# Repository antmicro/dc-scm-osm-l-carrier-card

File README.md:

# DC-SCM Carrier Card for OSM-L SoMs

Copyright (c) 2025 [Antmicro](https://www.antmicro.com)

## Overview

This project includes open hardware design files for a DC-SCM compliant PCB that supports System on Modules following the [OSM-L](https://sget.org/standards/osm/) standard specified by the SGet group.
The DC-SCM follows the interface and mechanical outline described in the 2.1 revision of the [DC-SCM standard](https://drive.google.com/file/d/1-SdSQvSWy5pNN_kBiyztblxE4jdyUe9W/view?usp=sharing) specified by the Open Compute Project community.
Apart from establishing a base DC-SCM compliant platform, the design includes a series of breakout connectors, jumpers and other supplementary circuitry for developing BMC software features for security, reliability, commissioning and benchmarking.

This DC-SCM card has been designed as a carrier board to an L-sized [OSM design](https://github.com/antmicro/osm-l-bmc-som) that combines a Lattice FPGA and an NXP i.MX943 series Application Processor (AP).

The PCB design files were prepared in [KiCad](kicad.org/download) 9.x

## Key features

* Landing pad for OSM-L type of SoM
* Realtek 1Gb Ethernet PHY (Realtek [RTL8211FDI-CG](https://openhardware.antmicro.com/components/realtek-rtl8211fdi-cg))
* ITE [IT6251](https://openhardware.antmicro.com/components/ite-tech-it6251) LVDS-DisplayPort bridge
* USB-C port with FTDI [FT4232H](https://openhardware.antmicro.com/components/ftdi-chip-ft4232h-56q-reel/) for SoM debug and software integration
* USB-C port connected to the OSM-L SoM pads
* USB-C port connected to the HPM
* M.2 (key-M) expansion slot connected to the HPM
* Slot for removable BIOS memories connected directly to the HPM
* Optional on-board TPM connector

## Project structure

The main directory contains KiCad PCB project files, a LICENSE and a README.
The remaining files are stored in the following directories:

* `doc` - contains board schematic
* `img` contains graphics for this README

## Licensing

This project is published under the [Apache-2.0](LICENSE) license.

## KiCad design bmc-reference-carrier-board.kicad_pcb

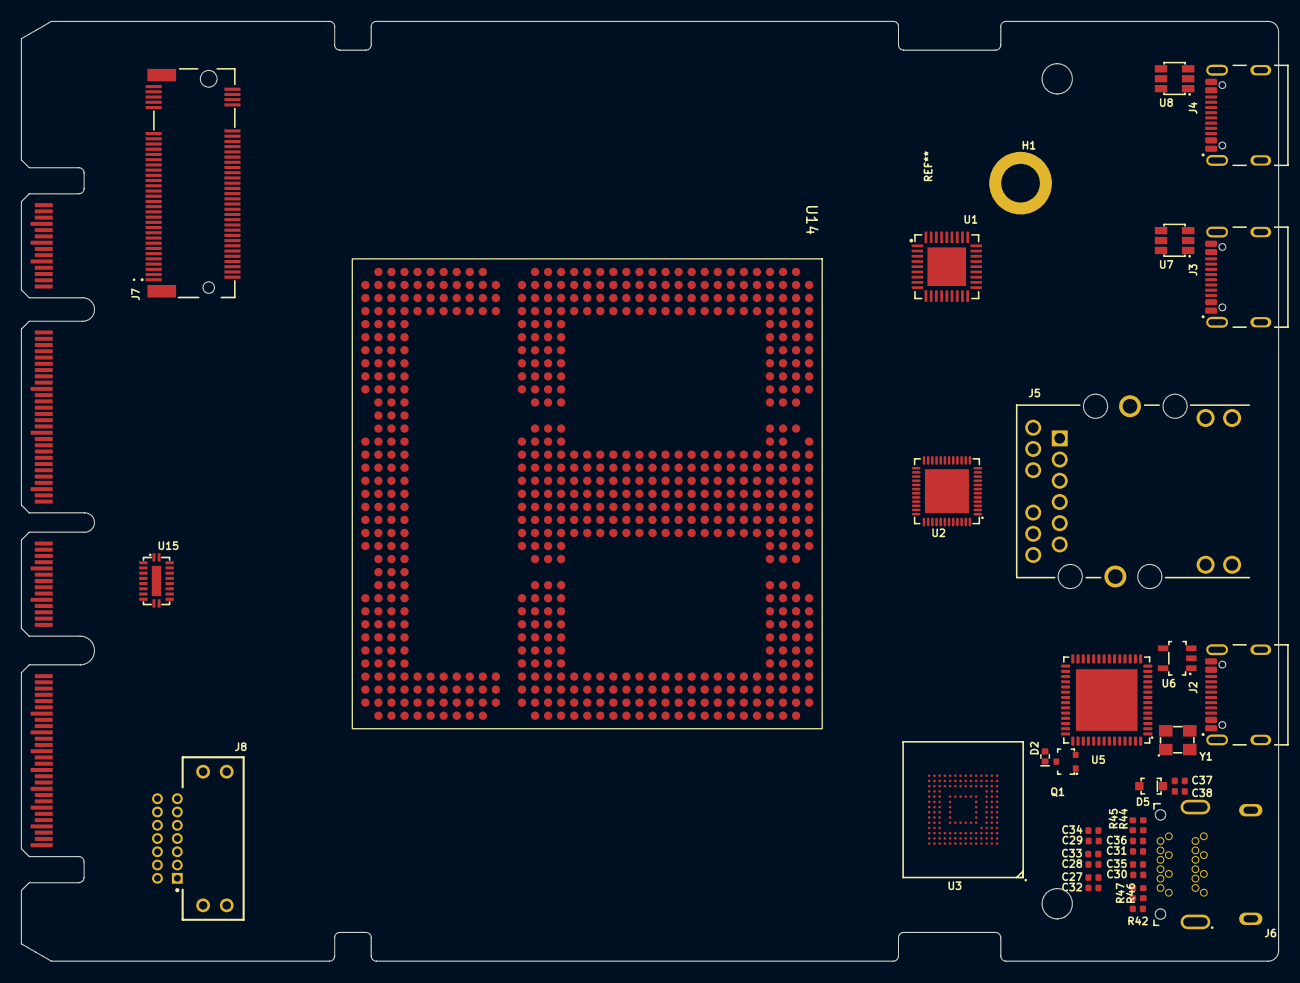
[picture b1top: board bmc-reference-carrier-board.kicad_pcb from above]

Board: 8 copper layers, 120.4 x 90.0 mm, 39 parts (0 on the bottom side), 56 nets, no tracks yet.

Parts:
C27, C28, C29, C30, C31, C32, C33, C34, C35, C36: C_100n_0402; C_0402_1005Metric
C37, C38: C_4u7_6.3V_0402; C_0402_1005Metric
D2: LED_G_0402_VLMTG1500-GS08; LED_0402_1005Metric_G
D5: 1N4148WS-7-F; D_SOD-323
H1: Spacer_Drill3.7mm_H2.5mm_9774025151R
J1: PCB-Edge_DC-SCM-2.1_2x84_Rev-1-1; PCB-Edge_DC-SCM_2x84_Rev-1-0
J2, J3, J4: USB-C_GCT_USB4105-GF-A; USB-C_Receptacle_GCT_USB4105-GF-A
J5: L834-1G1T-S7; RJ45_BEL_L834-1G1T-S7
J6: DisplayPort-Mini_TE_2129320-3; DisplayPort-Mini_Receptacle_TE_2129320-3
J7: Bus_M.2_1-2199230-6; Bus_M.2_Socket_Key_M_TE_1-2199230-6
J8: TFM-107-01-X-D-RE1-WT; Socket_Samtec_TFM_2x7_TFM-107-01-X-D-RE1-WT
Q1: BSS84AKW; SOT-323
R42: R_51k_0402; R_0402_1005Metric
R44, R45: R_100k_0402; R_0402_1005Metric
R46, R47: R_1M_0402; R_0402_1005Metric
U1: USB2514B-I_M2; QFN-36-1EP_6x6mm_P0.5mm_EP3.7x3.7mm
U2: RTL8211FS-CG; QFN-48-1EP_6x6mm
U3: SDINBDG4-8G; BGA-196-153_11.5x13mm_Layout14x14_P0.5x0.5mm
U5: FT4232H_VQFN; QFN-56-1EP_8x8mm_P0.5mm
U6: NCP718BSN330T1G; SOT-23-5
U7, U8: AP22615A_TSOT26; TSOT23-6
U14: OSM-L_Carrier-side
U15: CBTL02043ABQ; DHVQFN-20-1EP_2.5x4.5_P0.5mm
Y1: Resonator_12MHz_ABM8G; Resonator_SMD_Abracon_ABM8G_3.2x2.5mm

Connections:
+3V3: U15.1 (VDD), U15.6 (VDD), U15.10 (VDD)
+5V: U7.6 (IN), U8.6 (IN)
/DC-SCM 2.1 connector/DC_SCM_12V_AUX: J1.A1 (P12V_AUX), J1.A2 (P12V_AUX), J1.A3 (P12V_AUX), J1.A4 (P12V_AUX)
/DC-SCM 2.1 connector/DC_SCM_P3V0: J1.B28 (P3V0_HPM_SCM_BAT), U14.W17 (RTC_PWR)
/DC-SCM 2.1 connector/DC_SCM_PRSNT0_N: J1.A7 (PRSNT1_HPM_SCM_N), J1.B58 (PRSNT0_SCM_HPM_N)
/DC-SCM 2.1 connector/DC_SCM_USB1.D+: J3.A6 (D_{A}+), J3.B6 (D_{B}+)
/DC-SCM 2.1 connector/DC_SCM_USB1.D-: J3.A7 (D_{A}-), J3.B7 (D_{B}-)
/Ethernet PHY/ETHERNET.MDI0+: J5.11 (TRD1+), U2.2 (MDIP0)
/Ethernet PHY/ETHERNET.MDI0-: J5.10 (TRD1-), U2.3 (MDIN0)
/Ethernet PHY/ETHERNET.MDI1+: J5.4 (TRD2+), U2.5 (MDIP1)
/Ethernet PHY/ETHERNET.MDI1-: J5.5 (TRD2-), U2.6 (MDIN1)
/Ethernet PHY/ETHERNET.MDI2+: J5.3 (TRD3+), U2.7 (MDIP2)
/Ethernet PHY/ETHERNET.MDI2-: J5.2 (TRD3-), U2.8 (MDIN2)
/Ethernet PHY/ETHERNET.MDI3+: J5.8 (TRD4+), U2.10 (MDIP3)
/Ethernet PHY/ETHERNET.MDI3-: J5.9 (TRD4-), U2.11 (MDIN3)
/Front panel USB/FTDI_3V3: Q1.2 (S), U5.16 (V_{CCIO}), U5.36 (V_{CCIO}), U5.44 (V_{REGIN}), U5.50 (V_{CCIO}), U6.5 (VOUT)
/Front panel USB/USB0_VBUS: J3.A4 (VBUS), J3.A9 (VBUS), J3.B4 (VBUS), J3.B9 (VBUS), U7.1 (OUT)
/Front panel USB/USB1.D+: J4.A6 (D_{A}+), J4.B6 (D_{B}+)
/Front panel USB/USB1.D-: J4.A7 (D_{A}-), J4.B7 (D_{B}-)
/Front panel USB/USB1_VBUS: J4.A4 (VBUS), J4.A9 (VBUS), J4.B4 (VBUS), J4.B9 (VBUS), U8.1 (OUT)
/Front panel USB/USB2_D+: J2.A6 (D_{A}+), J2.B6 (D_{B}+), U5.8 (D+)
/Front panel USB/USB2_D-: J2.A7 (D_{A}-), J2.B7 (D_{B}-), U5.7 (D-)
/Front panel USB/USB2_VBUS: J2.A4 (VBUS), J2.A9 (VBUS), J2.B4 (VBUS), J2.B9 (VBUS), U6.1 (VIN), U6.3 (EN)
/Front panel USB/VCORE: U5.2 (V_{CORE}), U5.31 (V_{CORE}), U5.43 (V_{REGOUT})
/Front panel USB/XI: U5.3 (OSCI), Y1.1
/Front panel USB/XO: U5.4 (OSCO), Y1.3
/Front panel Video/AUX+: C31.1, J6.16 (AUX+), R45.2
/Front panel Video/AUX-: C36.1, J6.18 (AUX-), R44.1
/Front panel Video/CFG1: J6.4 (CFG1), R46.2
/Front panel Video/CFG2: J6.6 (CFG2), R47.2
/Front panel Video/DP_PWR: C37.2, C38.2, D5.1 (C), J6.20 (DP_PWR), R44.2
/Front panel Video/HPD: J6.2 (HPD), R42.1
/Front panel Video/TXD0+: C27.1, J6.3 (TXD0+)
/Front panel Video/TXD0-: C32.1, J6.5 (TXD0-)
/Front panel Video/TXD1+: C28.1, J6.9 (TXD1+)
/Front panel Video/TXD1-: C33.1, J6.11 (TXD1-)
/Front panel Video/TXD2+: C29.1, J6.15 (TXD2+)
/Front panel Video/TXD2-: C34.1, J6.17 (TXD2-)
/Front panel Video/TXD3+: C30.1, J6.10 (TXD3+)
/Front panel Video/TXD3-: C35.1, J6.12 (TXD3-)
GND: C37.1, C38.1, J1.A5 (GND), J1.A6 (GND), J1.A19 (GND), J1.A22 (GND), J1.A25 (GND), J1.A29 (GND), J1.A32 (GND), J1.A35 (GND), J1.A38 (GND), J1.A53 (GND), J1.A64 (GND), J1.A67 (GND), J1.A70 (GND), J1.B11 (GND), J1.B19 (GND), J1.B22 (GND), J1.B25 (GND), J1.B29 (GND), J1.B32 (GND), J1.B35 (GND), J1.B38 (GND), J1.B64 (GND), J1.B67 (GND), J1.B70 (GND), J1.OA1 (GND), J1.OA4 (GND), J1.OA7 (GND), J1.OA10 (GND), J1.OA13 (GND), J1.OB1 (GND), J1.OB4 (GND), J1.OB7 (GND), J1.OB10 (GND), J1.OB13 (GND), J2.A1 (GND), J2.A12 (GND), J2.B1 (GND), J2.B12 (GND), J3.A1 (GND), J3.A12 (GND), J3.B1 (GND), J3.B12 (GND), J4.A1 (GND), J4.A12 (GND), J4.B1 (GND), J4.B12 (GND), J6.1 (GND), J6.7 (GND), J6.8 (GND), J6.13 (GND), J6.14 (GND), J6.19 (GND), J6.SH, R45.1, R46.1, R47.1, U3.A6 (VSS), U3.C4 (VSSQ), U3.E7 (VSS), U3.G5 (VSS), U3.H10 (VSS), U3.J5 (VSS), U3.K8 (VSS), U3.N2 (VSSQ), U3.N5 (VSSQ), U3.P4 (VSSQ), U3.P6 (VSSQ), U5.10 (TEST), U5.21 (GND), U5.41 (GND), U5.45 (GND), U5.57 (GND), U6.2 (GND), U7.2 (GND), U8.2 (GND), U15.2 (XSD), U15.5 (GND), U15.11 (GND), U15.20 (GND), U15.21 (GND), Y1.2 (SH), Y1.4 (SH)
unnamed: D2.2 (A), Q1.3 (D)
unnamed: J5.1 (TRCT3), J5.6 (TRCT2), J5.7 (TRCT4), J5.12 (TRCT1)
unnamed: J7.2 (3V3), J7.4 (3V3), J7.12 (3V3), J7.14 (3V3), J7.16 (3V3), J7.18 (3V3), J7.70 (3V3), J7.72 (3V3), J7.74 (3V3)
unnamed: J7.1 (GND), J7.3 (GND), J7.9 (GND), J7.15 (GND), J7.21 (GND), J7.27 (GND), J7.33 (GND), J7.39 (GND), J7.45 (GND), J7.51 (GND), J7.57 (GND), J7.71 (GND), J7.73 (GND), J7.75 (GND)
unnamed: J7.MP1 (MP), J7.MP2 (MP)
unnamed: Q1.1 (G), U5.54 (~PWR_{EN})
unnamed: U1.15 (VDD33), U1.23 (VDD33)
unnamed: U1.5 (VDDA33), U1.10 (VDDA33), U1.29 (VDDA33), U1.36 (VDDA33)
unnamed: U2.4 (AVDD10), U2.9 (AVDD10), U2.47 (AVDD10)
unnamed: U2.1 (AVDD33), U2.12 (AVDD33), U2.30 (AVDD33)
unnamed: U3.E6 (VCC), U3.F5 (VCC), U3.J10 (VCC), U3.K9 (VCC)
unnamed: U3.C6 (VCCQ), U3.M4 (VCCQ), U3.N4 (VCCQ), U3.P3 (VCCQ), U3.P5 (VCCQ)
unnamed: U14.A4 (GND), U14.A7 (GND), U14.A10 (GND), U14.A26 (GND), U14.A29 (GND), U14.A32 (GND), U14.AA1 (GND), U14.AA4 (GND), U14.AA7 (GND), U14.AA8 (GND), U14.AA10 (GND), U14.AA11 (GND), U14.AA14 (GND), U14.AA17 (GND), U14.AA19 (GND), U14.AA22 (GND), U14.AA25 (GND), U14.AA26 (GND), U14.AA27 (GND), U14.AA28 (GND), U14.AA32 (GND), U14.AB3 (GND), U14.AB6 (GND), U14.AB9 (GND), U14.AB15 (GND), U14.AB21 (GND), U14.AB28 (GND), U14.AB31 (GND), U14.AB34 (GND), U14.AC4 (GND), U14.AC7 (GND), U14.AC10 (GND), U14.AC27 (GND), U14.AC30 (GND), U14.AC33 (GND), U14.AE2 (GND), U14.AE34 (GND), U14.AF35 (GND), U14.AG3 (GND), U14.AH2 (GND), U14.AH34 (GND), U14.AJ35 (GND), U14.AK3 (GND), U14.AL2 (GND), U14.AL34 (GND), U14.AM13 (GND), U14.AM16 (GND), U14.AM19 (GND), U14.AM22 (GND), U14.AM35 (GND), U14.AN3 (GND), U14.AN6 (GND), U14.AN9 (GND), U14.AN11 (GND), U14.AN15 (GND), U14.AN18 (GND), U14.AN21 (GND), U14.AN33 (GND), U14.AP2 (GND), U14.AP5 (GND), U14.AP8 (GND), U14.AP13 (GND), U14.AP16 (GND), U14.AP19 (GND), U14.AP22 (GND), U14.AP25 (GND), U14.AP28 (GND), U14.AP31 (GND), U14.AP34 (GND), U14.AR14 (GND), U14.AR17 (GND), U14.AR20 (GND), U14.AR26 (GND), U14.AR29 (GND), U14.AR32 (GND), U14.B2 (GND), U14.B5 (GND), U14.B8 (GND), U14.B9 (GND), U14.B27 (GND), U14.B28 (GND), U14.B30 (GND), U14.B33 (GND), U14.C11 (GND), U14.C25 (GND), U14.C32 (GND), U14.C35 (GND), U14.D1 (GND), U14.D5 (GND), U14.D8 (GND), U14.D18 (GND), U14.D28 (GND), U14.D34 (GND), U14.E2 (GND), U14.E15 (GND), U14.E21 (GND), U14.F16 (GND), U14.F20 (GND), U14.F33 (GND), U14.F35 (GND), U14.G34 (GND), U14.H2 (GND), U14.H4 (GND), U14.H32 (GND), U14.J16 (GND), U14.J20 (GND), U14.J33 (GND), U14.J35 (GND), U14.K32 (GND), U14.K34 (GND), U14.L2 (GND), U14.L4 (GND), U14.L18 (GND), U14.M16 (GND), U14.M20 (GND), U14.M32 (GND), U14.M35 (GND), U14.N34 (GND), U14.P2 (GND), U14.P4 (GND), U14.P18 (GND), U14.R1 (GND), U14.R16 (GND), U14.R20 (GND), U14.R32 (GND), U14.T34 (GND), U14.U2 (GND), U14.U4 (GND), U14.V1 (GND), U14.V16 (GND), U14.V20 (GND), U14.W3 (GND), U14.W34 (GND), U14.Y2 (GND), U14.Y18 (GND)
unnamed: U14.AE4 (VCC_IN_5V), U14.AF4 (VCC_IN_5V), U14.AG4 (VCC_IN_5V), U14.AH3 (VCC_IN_5V), U14.AH4 (VCC_IN_5V), U14.AJ3 (VCC_IN_5V), U14.AJ4 (VCC_IN_5V), U14.AK4 (VCC_IN_5V), U14.Y8 (VCC_IN_5V), U14.Y9 (VCC_IN_5V), U14.Y10 (VCC_IN_5V), U14.Y11 (VCC_IN_5V), U14.Y17 (VCC_IN_5V), U14.Y25 (VCC_IN_5V), U14.Y26 (VCC_IN_5V), U14.Y27 (VCC_IN_5V), U14.Y28 (VCC_IN_5V)
unnamed: U14.AA18 (V_BAT), U14.AB18 (V_BAT)

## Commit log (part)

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2025-08-19 [#81876] Add component and tracks keepout as defined in DC-SCM 2.1 spec
2025-08-19 [#81876] Add 8L stackup definition
2025-08-19 Add gitignore
2025-08-19 [#81876] Add automation
2025-08-19 [#81876] Create KiCad file structure. Define DC-SCM 2.1 edge and outline
2025-10-13 [#82176] Add passives to PCIe/USB mux
2025-10-13 [#81876] Add USB bus aliases
2025-10-13 [#82153] Add Mini DP passives
2025-10-13 [#81876] Add USB circuitry
2025-10-13 [#82176] Place PCIe/USB mux
2025-10-13 [#81876] Remove i.MX94 note
2025-10-13 [#81876] Rename osm_l.kicad_sch into osm_l_lowspeed_power
2025-10-13 [#81876] Add OSM subsheets
2025-10-13 [#81876] Add QSPI/eSPI mux sheet
2025-10-13 [#81876] Add USB symbols
2025-10-13 [#82176] Add Ethernet connections
2025-10-13 Replace {slash} with _
2025-10-13 [#82176] Fix conflicting annotations
2025-10-13 [#81876] Add remaining I2C channels
2025-10-13 [#82153] Move Ethernet bus definition to root schematic
2025-10-13 [#82176] Add placeholder eMMC
2025-10-13 [#82157] EMMC -> eMMC
2025-10-13 Add TPM connector
2025-10-13 [#81876] Continue adding top-level connections
2025-10-13 [#82153] Add AUX do DP bus alias
2025-10-13 [#81876] Update date, Regroup OSM L block to make it interchangeable
2025-10-13 [#81876] Replace OSM blocks with single A2 sheet
2025-10-13 [#82148] Replace PCIe/USB mux with TMUXHS4212IRKSR
    Update PCIe/USB mux sheet
2025-10-13 [#81978] Fix subsheet file naming
2025-10-13 [#81876] Add PCIe x4 connector
2025-10-13 [#81876] Improve USB shield RC circuit
2025-10-13 [#82157] Move JTAG and UART definitions to root sheet
2025-10-13 [#82153] Add DP bus alias
2025-10-13 [#82153] Fix LED2 label on ETH sheet
2025-10-13 [#81876] Add PCIe/SGMII mux
2025-10-13 [#82157] Add diode to DP_PWR
2025-10-13 [#81876] Add 0R to FTDI status LED
2025-10-13 [#82157] Labels on root sheet from Ethernet and video sheets
2025-10-13 [#82153] Cleanup RC next to Eth connector
2025-10-13 [#82153] Add RJ45 connector
2025-10-13 [#85165] Add LICENSE
2025-10-13 [#81876] Add power section
2025-10-13 [#81876] Hierarchical design review fixes
2025-10-13 [#81876] Add PCIe C&D
2025-10-13 [#82226] Add PCIe/SGMII mux
2025-10-13 Add PCIe x4 connector (M.2 key M)
2025-10-13 [#81876] Add FTDI chip, DBG USB and LDO
2025-10-13 [#82153] Finalize video schematic
2025-10-13 [#82176] Add M.2 and TPM connectors
2025-10-13 [#82323] Update page numbers
2025-10-13 [#82226] Add PCIe connection to PCIe x4 connector
2025-10-13 [#82341] LVDS/DP Bridge: Start placing pasive components
2025-10-13 [#82147] Add notes about required power buses
2025-10-13 [#82323] Add NC-SI bus definition
2025-10-13 [#82323] Add PCIeREFCLK bus, update DC-SCM labels
2025-10-13 [#82190] Update Mini DP connector from library
2025-10-13 Add CC controllers to USB0 and USB1
2025-10-13 [#82176] Add M.2 standoff, update placement
2025-10-13 Replace Eth connector with 7498111120R
2025-10-13 [#82323] Connect RGMII to RTL8211FS-CG
2025-10-13 [#82190] Add light pipes
2025-10-13 [#82323] Connect NC-SI, QSPI, LTPI and UART buses to DC-SCM
2025-10-13 Change USB0 and USB1 to advertise as 500mA source
2025-10-13 [#82190] Update PCB from schematic
2025-10-13 [#82323] Add note about PECI voltage translator
2025-10-13 [#82323] ESPI -> eSPI
2025-10-13 [#82190] Lock key components and dimensions
2025-10-13 [#82323] Connect OSM signals
2025-10-13 [#82226] Extend PCIe bus definition to x4. Update hierarchical pins
2025-10-13 [#82323] Connect SDIO to OSM, prepare LVDS connections
2025-10-13 [#82323] Add CS1 to SPI bus
2025-10-13 Add series resistors to JTAG lines
2025-10-13 Replace USB-C connectors with vertical version
2025-10-13 Replace Mini DP connector with E9320-001-01
2025-10-13 [#82190] Add logotype
2025-10-13 [#82176] Import components from schematic and create initial placement
2025-10-13 Add light pipe and one additional LED
2025-10-13 Add USB Hub, start selecting strap options
2025-10-13 [#82190] Add cutout for Eth connector
2025-10-13 [#82190] Arrange components and lock HMI connectors position
2025-10-13 [#82323] Update OSM connections
    Move LTPI to LVSD pins
    Move I2C 0/1/2/3 lanes to vendor defined pins
    Move I2C/I3C 16/17 to GPIOD
    Add ~PRSNT1 as GPIO_A_3
    Add ~IRQ0 as GPIO_A_2
    Add ~STDB_RDY as GPIO_A_1
2025-10-13 [#82190] Change DC/DC coils to SRP3212A
2025-10-13 [#82323] Connect JTAG, USB, TPM, IxC and SPI buses to DC-SCM
2025-10-13 [#82323] Connect PCIe on DC-SCM
2025-10-13 [#83329] Change ETH PHY IC from RTL8211FS-CG to RTL8211FDI-CG
2025-10-13 [#83146] Fix LTPI connection, add bias
2025-10-13 [#83148] Connect the level shifters, change STBY bus to individual signals
2025-10-13 [#82233] Added eSPI/QSPI mux and DNP QSPI flash memory
2025-10-13 Added level shifter bypass
2025-10-13 [#82341] LVDS/DP Bridge: Add 1V2 and 1V8 LDOs
2025-10-13 Import changes to PCB
2025-10-13 [#83363] Added LVDS termination
2025-10-13 [#83329] Connect power, and remaining signals
2025-10-13 [#82176] Connect eMMC SDIO to OSM, annotate eMMC schematic
2025-10-13 [#82341] LVDS/DP Bridge: Add clock generator
2025-10-13 [#83338] Low speed PCIe x4 connections
2025-10-13 [#82341] LVDS/DP Bridge: Update power supply
2025-10-13 [#83338] Fixed PCIe TX/RX
2025-10-13 [#82687] Add IT6251 to schematic
2025-10-13 [#82341] LVDS/DP Bridge: Connect to OSM
2025-10-13 Changed A4 sheets to A3 and cleaned them up
2025-10-13 [#82684] Round cut-out area corners R=1mm
2025-10-13 Annotate schematic
2025-10-13 [#83329] Finish connecting ETH PHY, connect ETH LEDs, adjust PHY power supply filtering
2025-10-13 [#83146] Set LTPI bias voltage
2025-10-13 [#83329] Connect LEDs, crystal resontor, MDIO and MDC to the ETH PHY
2025-10-13 [#83363] Replaced 1V8 LDO with DC/DC and moved it to power sheet
2025-10-13 [#83337] Finalized PCIe-SGMII mux and PCIe-USB mux
2025-10-13 [#82687] Use 500mA LDO
2025-10-13 [#82688] Add 0R to dc-scm conn
2025-10-13 [#83363] Adjusted DP PWR connection
2025-10-13 [#83148] Add level shifters for i2c & stby
2025-10-13 [#82684] Add rectangular cut-out area
2025-10-13 [#83147] Fix spi labels
2025-10-13 [#83609] Move +5V to double switch. Add indicator LEDs and TPs
2025-10-13 [#83362] Remove bad NC marks, small visual fixes
2025-10-13 [#83362] Add headers to LTPI, PECI and I2C
2025-10-13 [#82323] Update OSM connector pinout
2025-10-13 [#83652] Add ability to program BIOS SPI flash
2025-10-13 [#83609] Add PWR_EN input
2025-10-13 [#83736] WIP: Clear ERC
2025-10-13 [#83336] Small front panel interface fixes
2025-10-13 [#83362] Add temperature sensors
2025-10-13 [#83609] Connect PWR_EN signal, change eMMC power to AON, minor schematic refactor
2025-10-13 [#83329] Small ethernet PHY fixes
2025-10-13 [#83609] Add power pushbutton
2025-10-13 [#83609] Add power push button emulator
2025-10-13 [#83736] Update DC-SCM connector from library
2025-10-13 [#83331] Added PECI circuitry. Small top fixes
2025-10-13 [#83736] Update devkit connectors pinout
2025-10-13 [#83736] Fix overlaping text and graphics, fix notes regarding USB-C role
2025-10-13 [#83362] Fix connections of headers, add I2C mux
2025-10-13 [#83329] Add TVS to Ethernet pins
2025-10-13 [#83736] Change the 5V DC-DC conveter with more powerful one, refactor power schematic sheet
2025-10-13 [#83609] Reannotate board
2025-10-13 [#83609] Connect all OSM signals
2025-10-13 [#83736] Update OSM connector from library, ERC is clear
2025-10-13 [#83336] Improved USB circuitry
2025-10-13 [#83329] Update ETH PHY IC footprint
2025-10-13 [#83736] Move LTPI bias from TX to RX, minor refactor
2025-10-13 [#83767] Define impedances
2025-10-13 [#83767] Set design constraints and physical stackup
2025-10-13 [#83767] WIP: Layout M.2 connector
2025-10-13 [#83904] Connect OSM_I2C_A bus to temperature sensors via 0Rs
2025-10-13 [#83904] Add level shifters, clear ERC
2025-10-13 [#83904] Add current monitoring IC to the 12V input rail
2025-10-13 [#83767] Fix overlaping graphics, add termination to RX_E1
2025-10-13 [#83767] Layout DC-DC converters, change 0R on power rails to one that can handle more current
2025-10-13 [#83767] Power Y5 from 3.3V rail
2025-10-13 [#83767] Connect J11 to U32 without R0
2025-10-13 [#83767] Replace USB Hub clk generator with crystal to align with reference design
2025-10-13 [#83767] Add alternative reset signal
2025-10-13 [#83767] Continue placement and routing
2025-10-13 [#83767] Add button debouncing
2025-10-13 [#83767] Remove FFC Eth connector
2025-10-13 [#83767] Replace BIOS flash with SO-16 package
2025-10-13 [#83767] Remove single lightpipe
2025-10-13 [#83767] Add MDIO pullup
2025-10-13 [#83767] Fix U5 SEL signal voltage
2025-10-13 [#83767] Cleanup USB2422 REM strap net names
2025-10-13 [#83767] Add USB SS RX/TX swap note
2025-10-13 [#83767] Add SGMII RX/TX swap note
    Fix signal level on U26 SEL pin
2025-10-13 [#83767] Connect ESD only to USB data lines
    CC lines have ESD inside CC controller
2025-10-13 [#83767] Bias LTPI after connector/OSM split
2025-10-13 [#83767] Remove redundant OSM 0R on LTPI
    Bias circuitry can be used as path selection
2025-10-13 [#83767] Disable PCIe x4
2025-10-13 [#83767] Disable NC-SI connection
2025-10-13 [#83767] Add GND test point
2025-10-13 [#83767] Remove redundant 0R on USB_A
2025-10-13 [#83767] Route power
2025-10-13 Assign DSI as 100Ohm diff
2025-10-13 [#83767] Update PCB from schematic
2025-10-13 [#83767] Reduce TMUXHS4212IRKSR decoupling
    Datasheet suggests 100nF
2025-10-13 [#83767] Continue placement
2025-10-13 [#83767] Disable LVDS
2025-10-13 [#83767] Make bypass USB a diff pair
2025-10-13 [#83767] Zone for 5V_AON
2025-10-13 [#83767] Fixup DRU
2025-10-13 [#83767] Replace RTL8211FDI-CG oscillator
2025-10-13 [#83767] Remove PCIe/USB SS passives
2025-10-13 [#83767] Assign net class to bypass LTPI
2025-10-13 [#83767] Place components around RTL8211FDI-CG
2025-10-13 [#83767] Move UART on FTDI from BDBUS
2025-10-13 [#83767] Add buttons to I2C_14
2025-10-13 [#83767] Add 12V DC input connector and BOOT_SEL switch
2025-10-13 [#83767] Sync PCB from schematic
2025-10-13 [#83767] Change TPM connector to one with correct pitch
2025-10-13 [#83767] Add more I2C connections
2025-10-13 [#83767] Position connectors
2025-10-13 [#83767] Route LTPI
2025-10-13 [#83767] Layout RGMII
2025-10-13 [#83767] Connect BOOT_SEL switch
2025-10-13 [#83767] Layout eMMC
2025-10-13 [#83767] Connect OSM GND
2025-10-13 [#83767] Layout buttons
2025-10-13 [#83767] Disable SCMC_CTRL SPI
2025-10-13 [#83767] Disable I2C_I3C_15
2025-10-13 [#83767] WIP: Layout ESPI and I2C
2025-10-13 [#83767] Disable QSPI to IMX and HPM JTAG
2025-10-13 [#83767] Clean DRC warnings. Add signage
2025-10-13 [#83767] Clean DRC errors
2025-10-13 [#83767] Improve power planes. Deskew USB
2025-10-13 [#83767] Set eMMC pins as free
2025-10-13 [#83767] Route all remaining signals
2025-10-13 [#83767] Improve reference planes
2025-10-13 [#84619] Remove debug connectors and backup ICs
2025-10-13 [#85165] README - expand features, add photo
2025-10-13 [#83767] Improve silkscreen marking
2025-10-13 [#84615] Connect Vbus detection to OSM
2025-10-13 [#84616] Add level shifters on FTDI signals
2025-10-13 [#84768] Sch: Complete top level connections
2025-10-13 [#84768] PCB: Initial PCIe0 routing
2025-10-13 [#84850] Change stackup to 10L; Update design rules
2025-10-13 [#84850] Move HS traces from case mounting area
2025-10-13 [#84768] Add missing connections on sch
2025-10-13 [#84850] Move 5V DCDC to top
2025-10-13 [#84846] Clean OSM cutout areas
2025-10-13 [#84846] Update plane assignment; Rough DSI routing
2025-10-13 [#84846] Update design rules; Rough RGMII routing
2025-10-13 [#85191] Reconnect APVDD pin of IT6251
2025-10-13 [#85165] README: Update naming
2025-10-13 [#84768] Bump revision, continue routing
2025-10-14 [#84768] Finish clearing DRC
2025-10-14 [#84768] Optimize routing
2025-10-14 README: Add links
2025-10-14 [#84768] Match RGMII
2025-10-14 [#84768] Match USB skew
2025-10-14 [#84768] Match NC-SI
2025-10-14 [#84768] Match DSI
2025-10-14 [#84768] Minor improvments
2025-10-14 [#84768] Match PCIe skew
2025-11-06 Add higher M.2 key M connector
2025-11-06 Add testpoints to QSPI, Clean DRC
2025-11-13 Change TPM connector
2025-11-13 Add I2C connector
2025-11-13 Fix missing connections. Clean ERC
2025-11-13 Remove sch files with debug circuitry
2025-11-14 Add schematic PDF

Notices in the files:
parts and their libraries:
License: Apache-2.0
